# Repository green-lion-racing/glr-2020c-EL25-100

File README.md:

# 2020c-EL25-100
 Green Lion Racing - Shutdown Relays

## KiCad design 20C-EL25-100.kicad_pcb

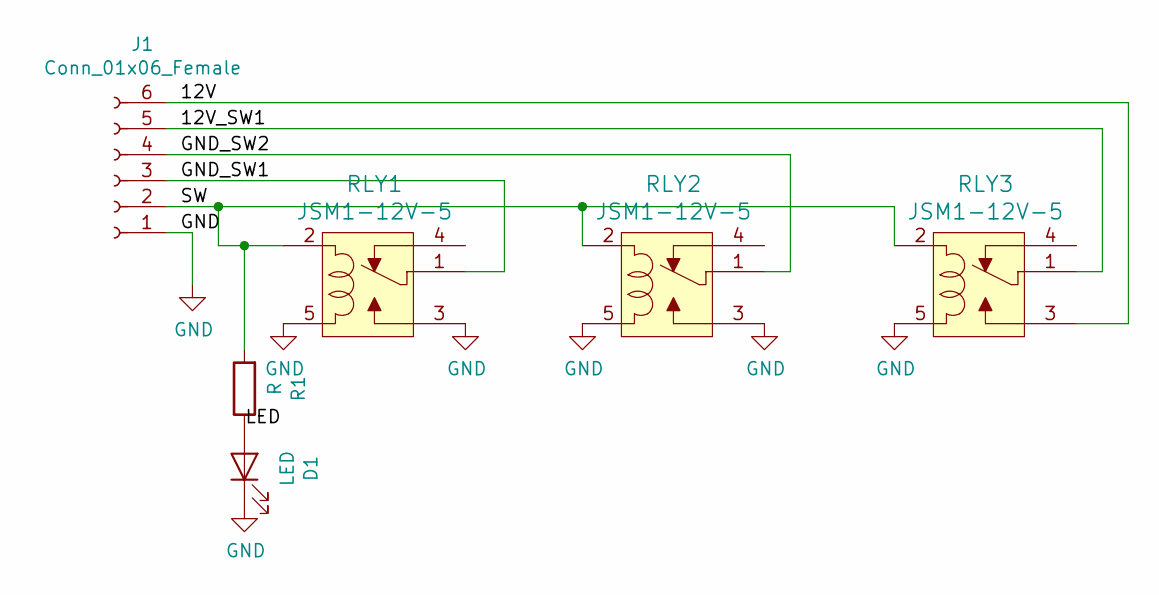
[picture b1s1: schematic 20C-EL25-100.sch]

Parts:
D1: LED; LED_PLCC-2
J1: Conn_01x06_Female; Molex_Mega-Fit_76825-0006_2x03_P5.70mm_Horizontal
R1: R; R_0603_1608Metric_Pad1.05x0.95mm_HandSolder
RLY1, RLY2, RLY3: JSM1-12V-5; Relay_JSM1-12V-5; MPN JSM1-12V-5; Digi-Key_PN 255-1240-ND

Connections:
/12V: J1.6, RLY3.3 (NO)
/12V_SW1: J1.5, RLY3.1 (COM)
/GND_SW1: J1.3, RLY1.1 (COM)
/GND_SW2: J1.4, RLY2.1 (COM)
/LED: D1.2 (A), R1.1
/SW: J1.2, R1.2, RLY1.2, RLY2.2, RLY3.2
GND: D1.1 (K), J1.1, RLY1.3 (NO), RLY1.5, RLY2.3 (NO), RLY2.5, RLY3.5

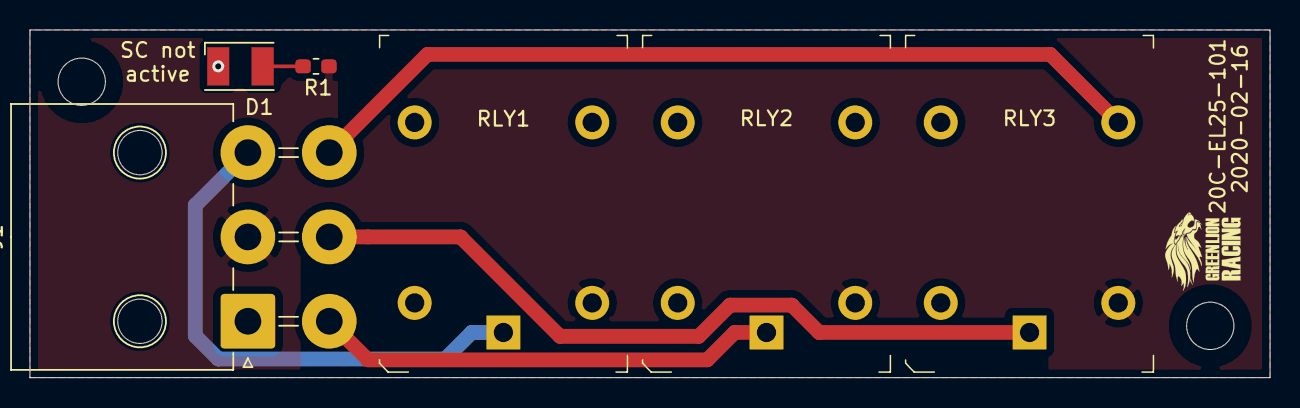
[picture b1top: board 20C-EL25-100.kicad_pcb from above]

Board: 2 copper layers, 83.8 x 23.5 mm, 6 parts (0 on the bottom side), 7 nets.

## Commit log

2020-02-15 changed shematic to 3 Relays
    Added Relays for Ignition as it needs 12V switched, not GND.
2020-02-15 Added submodule digikey
2020-02-16 added 3. relays to pcb
    added 12V relays on pcb to support our ignition (lowside FET inside MCU)
2025-02-08 remove temp files
